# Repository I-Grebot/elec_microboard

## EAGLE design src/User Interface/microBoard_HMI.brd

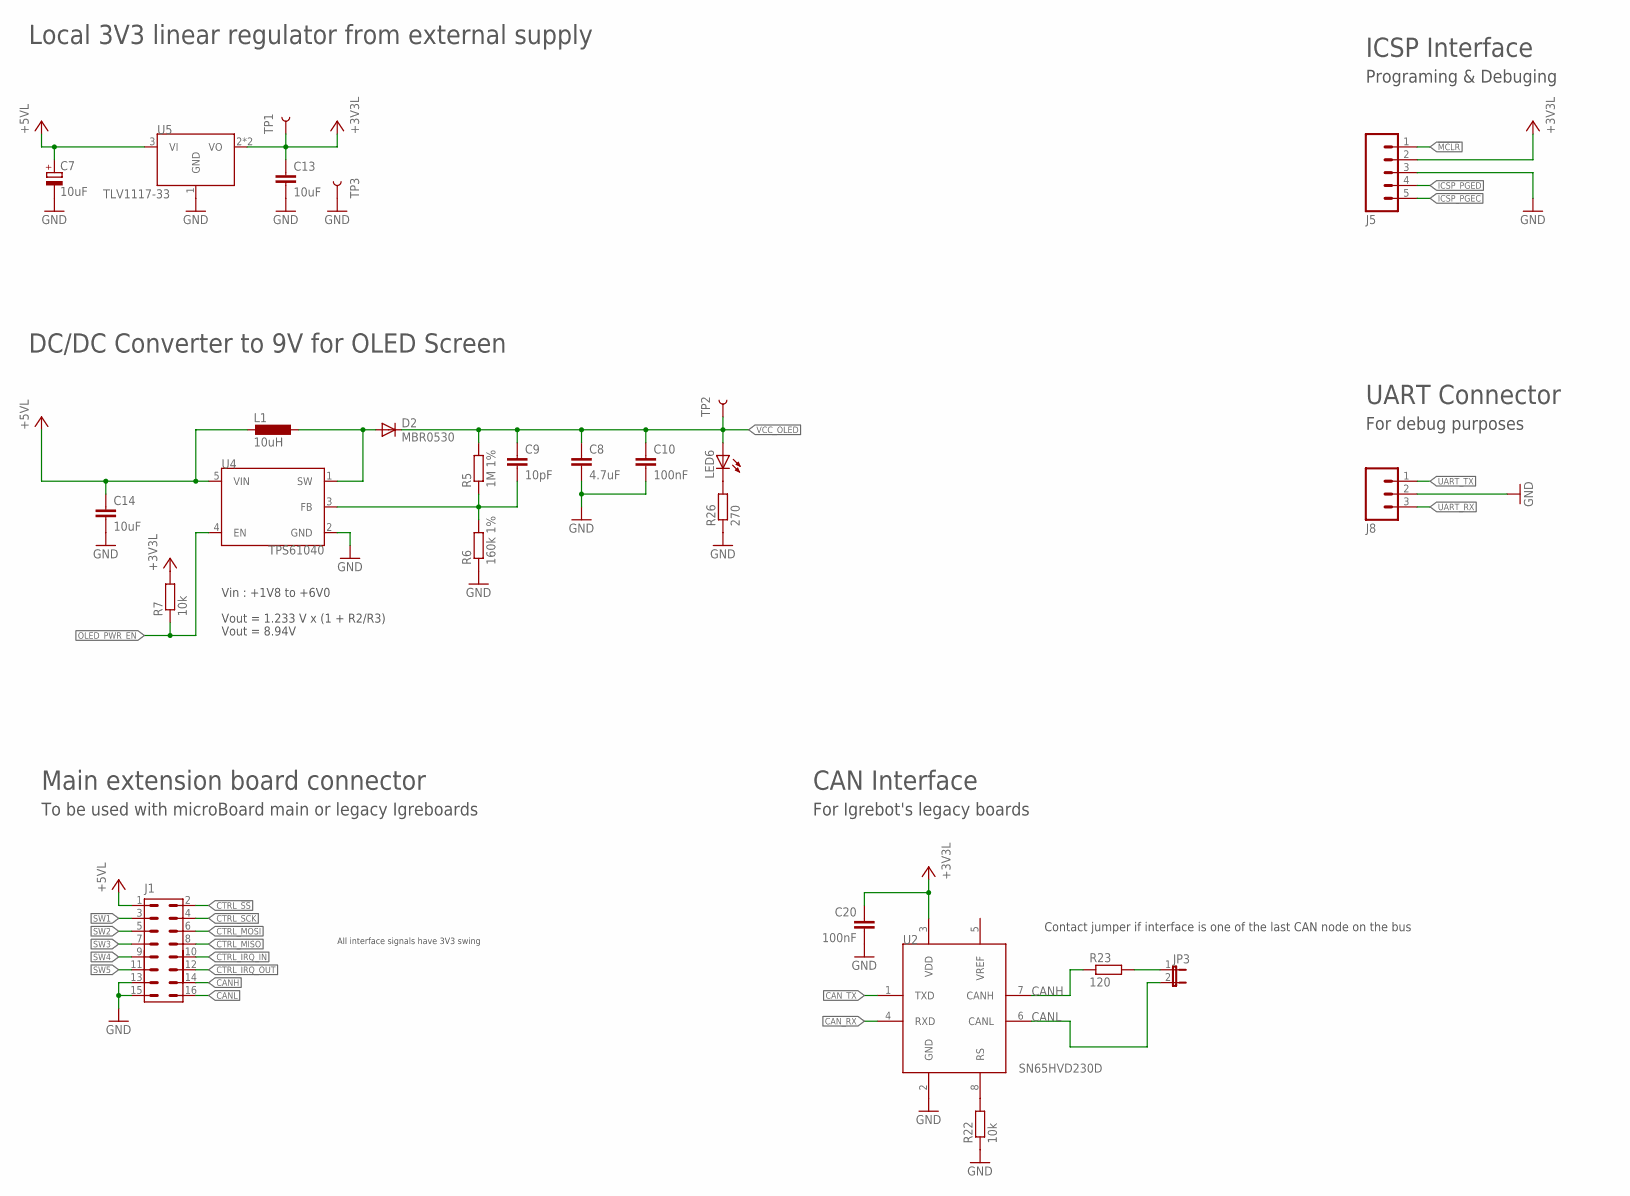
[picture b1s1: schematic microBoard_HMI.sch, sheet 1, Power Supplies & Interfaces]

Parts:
C7: 10uF; PANASONIC_C
C8: 4.7uF; C1206
C9: 10pF; C0603
C10, C20: 100nF; C0603
C13, C14: 10uF; C1206
D2: MBR0530; SOD-123_MINI-SMA
J1: HE10_H_16; CON_2X_2.54_H_16
J5: M05LOCK; 1X05_LOCK
J8: M03LOCK; 1X03_LOCK
JP3: JUMPER-2PTH_LOCK; 1X02_LOCK
L1: 10uH; L5650M
LED6: LEDCHIP-LED0805; CHIP-LED0805
R5: 1M 1%; R0603
R6: 160k 1%; R0603
R7, R22: 10k; R0603
R23: 120; R0603
R26: 270; R0603
TP1, TP2, TP3: TEST-POINT3X5; PAD.03X.05
U2: SN65HVD230D; SO-08
U4: TPS61040; SOT-23
U5: TLV1117-33; SOT_223

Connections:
!MCLR!: J5.1; also elsewhere on the board
+3V3L: C13.1, C20.1, J5.2, R7.2, TP1.P$1, U2.3 (VDD), U5.2 (VO), U5.4 (VO); also elsewhere on the board
+5VL: C7.+, C14.1, J1.1, L1.2, U4.5 (VIN), U5.3 (VI); also elsewhere on the board
CANH: J1.14, R23.1, U2.7 (CANH)
CANL: J1.16, JP3.2, U2.6 (CANL)
CAN_RX: U2.4 (RXD); also elsewhere on the board
CAN_TX: U2.1 (TXD); also elsewhere on the board
CTRL_!SS!: J1.2; also elsewhere on the board
CTRL_IRQ_IN: J1.10; also elsewhere on the board
CTRL_IRQ_OUT: J1.12; also elsewhere on the board
CTRL_MISO: J1.8; also elsewhere on the board
CTRL_MOSI: J1.6; also elsewhere on the board
CTRL_SCK: J1.4; also elsewhere on the board
GND: C7.-, C8.2, C10.2, C13.2, C14.2, C20.2, J1.13, J1.15, J5.3, J8.2, R6.1, R22.1, R26.1, TP3.P$1, U2.2 (GND), U4.2 (GND), U5.1 (GND); also elsewhere on the board
ICSP_PGEC: J5.5; also elsewhere on the board
ICSP_PGED: J5.4; also elsewhere on the board
unnamed: D2.A, L1.1, U4.1 (SW)
unnamed: C9.2, R5.1, R6.2, U4.3 (FB)
unnamed: LED6.C, R26.2
unnamed: JP3.1, R23.2
unnamed: R22.2, U2.8 (RS)
OLED_PWR_EN: R7.1, U4.4 (EN); also elsewhere on the board
SW1: J1.3; also elsewhere on the board
SW2: J1.5; also elsewhere on the board
SW3: J1.7; also elsewhere on the board
SW4: J1.9; also elsewhere on the board
SW5: J1.11; also elsewhere on the board
UART_RX: J8.3; also elsewhere on the board
UART_TX: J8.1; also elsewhere on the board
VCC_OLED: C8.1, C9.1, C10.1, D2.C, LED6.A, R5.2, TP2.P$1; also elsewhere on the board

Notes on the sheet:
Vin : +1V8 to +6V0
Vout = 1.233 V x (1 + R2/R3)
Vout = 8.94V
Local 3V3 linear regulator from external supply
DC/DC Converter to 9V for OLED Screen
To be used with microBoard main or legacy Igreboards
Main extension board connector
Programing & Debuging
ICSP Interface
All interface signals have 3V3 swing
For debug purposes
UART Connector
For Igrebot's legacy boards
CAN Interface
Contact jumper if interface is one of the last CAN node on the bus

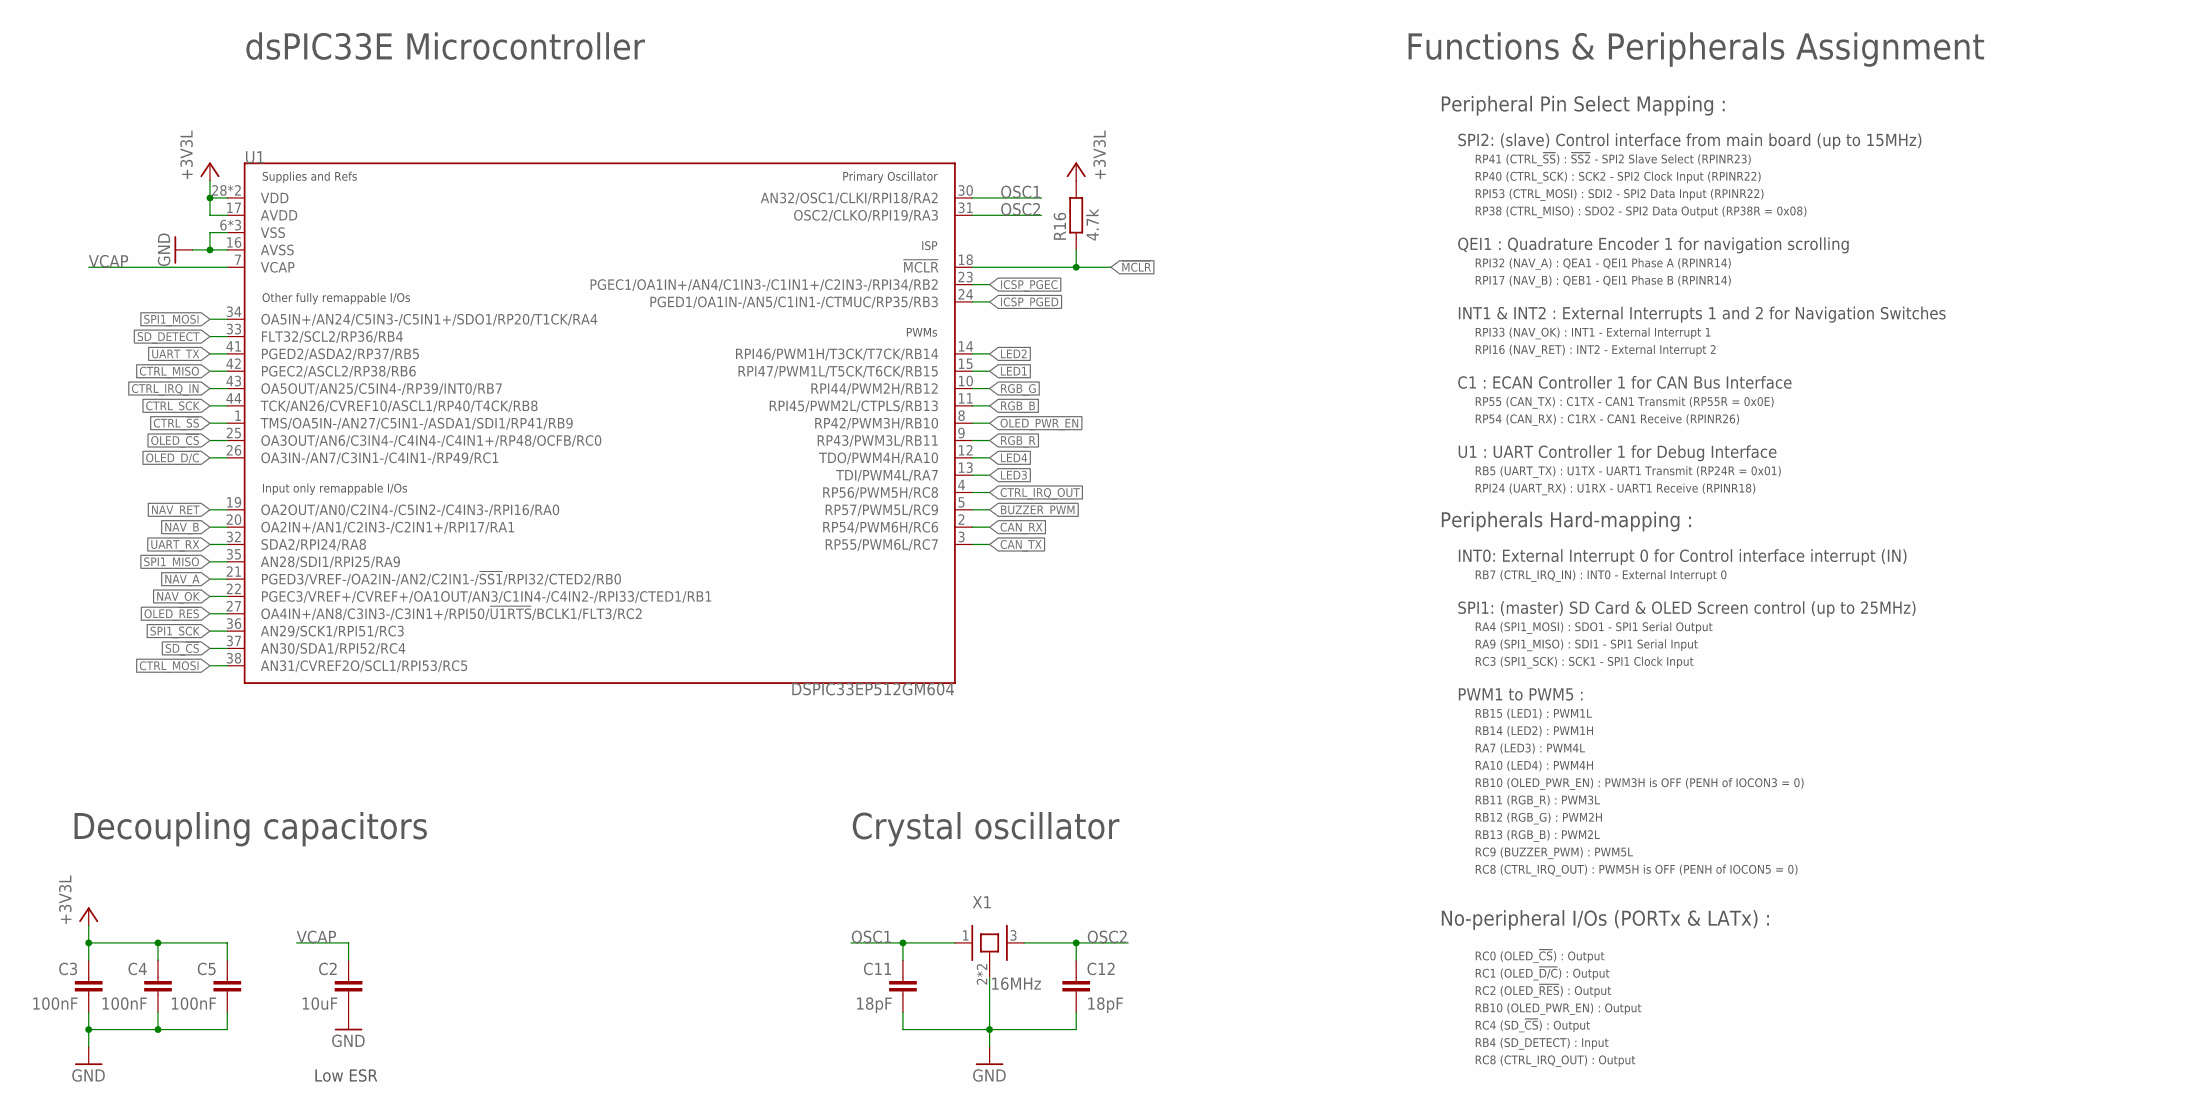
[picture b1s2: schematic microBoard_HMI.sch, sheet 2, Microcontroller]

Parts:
C2: 10uF; C1206
C3, C4, C5: 100nF; C0603
C11, C12: 18pF; C0603
R16: 4.7k; R0603
U1: DSPIC33EP512GM604; TQFP_44
X1: 16MHz; CRYSTAL-OSC-SMD-5X3

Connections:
!MCLR!: R16.1, U1.18 (!MCLR!); also elsewhere on the board
+3V3L: C3.1, C4.1, C5.1, R16.2, U1.17 (AVDD), U1.28 (VDD), U1.40 (VDD); also elsewhere on the board
BUZZER_PWM: U1.5 (RP57/PWM5L/RC9); also elsewhere on the board
CAN_RX: U1.2 (RP54/PWM6H/RC6); also elsewhere on the board
CAN_TX: U1.3 (RP55/PWM6L/RC7); also elsewhere on the board
CTRL_!SS!: U1.1 (TMS/OA5IN-/AN27/C5IN1-/ASDA1/SDI1/RP41/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); also elsewhere on the board
CTRL_IRQ_IN: U1.43 (OA5OUT/AN25/C5IN4-/RP39/INT0/RB7); also elsewhere on the board
CTRL_IRQ_OUT: U1.4 (RP56/PWM5H/RC8); also elsewhere on the board
CTRL_MISO: U1.42 (PGEC2/ASCL2/RP38/RB6); also elsewhere on the board
CTRL_MOSI: U1.38 (AN31/CVREF2O/SCL1/RPI53/RC5); also elsewhere on the board
CTRL_SCK: U1.44 (TCK/AN26/CVREF10/ASCL1/RP40/T4CK/RB8); also elsewhere on the board
GND: C2.2, C3.2, C4.2, C5.2, C11.2, C12.2, U1.6 (VSS), U1.16 (AVSS), U1.29 (VSS), U1.39 (VSS), X1.2, X1.4; also elsewhere on the board
ICSP_PGEC: U1.23 (PGEC1/OA1IN+/AN4/C1IN3-/C1IN1+/C2IN3-/R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); also elsewhere on the board
ICSP_PGED: U1.24 (PGED1/OA1IN-/AN5/C1IN1-/CTMUC/RP35/RB3); also elsewhere on the board
LED1: U1.15 (RPI47/PWM1L/T5CK/T6CK/RB15); also elsewhere on the board
LED2: U1.14 (RPI46/PWM1H/T3CK/T7CK/RB14); also elsewhere on the board
LED3: U1.13 (TDI/PWM4L/RA7); also elsewhere on the board
LED4: U1.12 (TDO/PWM4H/RA10); also elsewhere on the board
NAV_A: U1.21 (PGED3/VREF-/OA2IN-/AN2/C2IN1-/!SS1!/RPI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); also elsewhere on the board
NAV_B: U1.20 (OA2IN+/AN1/C2IN3-/C2IN1+/RPI17/RA1); also elsewhere on the board
NAV_OK: U1.22 (PGEC3/VREF+/CVREF+/OA1OUT/AN3/C1IN4-/C4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); also elsewhere on the board
NAV_RET: U1.19 (OA2OUT/AN0/C2IN4-/C5IN2-/C4IN3-/RPI16/R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); also elsewhere on the board
OLED_!CS!: U1.25 (OA3OUT/AN6/C3IN4-/C4IN4-/C4IN1+/RP48/OC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); also elsewhere on the board
OLED_!D/C!: U1.26 (OA3IN-/AN7/C3IN1-/C4IN1-/RP49/RC1); also elsewhere on the board
OLED_!RES!: U1.27 (OA4IN+/AN8/C3IN3-/C3IN1+/RPI50/!U1RTS!/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); also elsewhere on the board
OLED_PWR_EN: U1.8 (RP42/PWM3H/RB10); also elsewhere on the board
OSC1: C11.1, U1.30 (AN32/OSC1/CLKI/RPI18/RA2), X1.1
OSC2: C12.1, U1.31 (OSC2/CLKO/RPI19/RA3), X1.3
RGB_B: U1.11 (RPI45/PWM2L/CTPLS/RB13); also elsewhere on the board
RGB_G: U1.10 (RPI44/PWM2H/RB12); also elsewhere on the board
RGB_R: U1.9 (RP43/PWM3L/RB11); also elsewhere on the board
SD_!CS!: U1.37 (AN30/SDA1/RPI52/RC4); also elsewhere on the board
SD_DETECT: U1.33 (FLT32/SCL2/RP36/RB4); also elsewhere on the board
SPI1_MISO: U1.35 (AN28/SDI1/RPI25/RA9); also elsewhere on the board
SPI1_MOSI: U1.34 (OA5IN+/AN24/C5IN3-/C5IN1+/SDO1/RP20/T1C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); also elsewhere on the board
SPI1_SCK: U1.36 (AN29/SCK1/RPI51/RC3); also elsewhere on the board
UART_RX: U1.32 (SDA2/RPI24/RA8); also elsewhere on the board
UART_TX: U1.41 (PGED2/ASDA2/RP37/RB5); also elsewhere on the board
VCAP: C2.1, U1.7 (VCAP)

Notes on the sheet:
SPI2: (slave) Control interface from main board (up to 15MHz)
dsPIC33E Microcontroller
Functions & Peripherals Assignment
Decoupling capacitors
Low ESR
Crystal oscillator
Peripheral Pin Select Mapping :
RB4 (SD_DETECT) : Input
RB5 (UART_TX) : U1TX - UART1 Transmit (RP24R = 0x01)
RPI53 (CTRL_MOSI) : SDI2 - SPI2 Data Input (RPINR22)
RP38 (CTRL_MISO) : SDO2 - SPI2 Data Output (RP38R = 0x08)
RP40 (CTRL_SCK) : SCK2 - SPI2 Clock Input (RPINR22)
RP41 (CTRL_!SS!) : !SS2! - SPI2 Slave Select (RPINR23)
RC0 (OLED_!CS!) : Output
No-peripheral I/Os (PORTx & LATx) :
RC1 (OLED_!D/C!) : Output
RPI16 (NAV_RET) : INT2 - External Interrupt 2
RPI17 (NAV_B) : QEB1 - QEI1 Phase B (RPINR14)
RPI24 (UART_RX) : U1RX - UART1 Receive (RPINR18)
Peripherals Hard-mapping :
RPI32 (NAV_A) : QEA1 - QEI1 Phase A (RPINR14)
RPI33 (NAV_OK) : INT1 - External Interrupt 1
RC2 (OLED_!RES!) : Output
RC4 (SD_!CS!) : Output
RB7 (CTRL_IRQ_IN) : INT0 - External Interrupt 0
RP55 (CAN_TX) : C1TX - CAN1 Transmit (RP55R = 0x0E)
RP54 (CAN_RX) : C1RX - CAN1 Receive (RPINR26)
RB10 (OLED_PWR_EN) : Output
RC8 (CTRL_IRQ_OUT) : Output
RA4 (SPI1_MOSI) : SDO1 - SPI1 Serial Output
RA9 (SPI1_MISO) : SDI1 - SPI1 Serial Input
RC3 (SPI1_SCK) : SCK1 - SPI1 Clock Input
PWM1 to PWM5 :
SPI1: (master) SD Card & OLED Screen control (up to 25MHz)
INT1 & INT2 : External Interrupts 1 and 2 for Navigation Switches
QEI1 : Quadrature Encoder 1 for navigation scrolling
C1 : ECAN Controller 1 for CAN Bus Interface
U1 : UART Controller 1 for Debug Interface
RB15 (LED1) : PWM1L
RB14 (LED2) : PWM1H

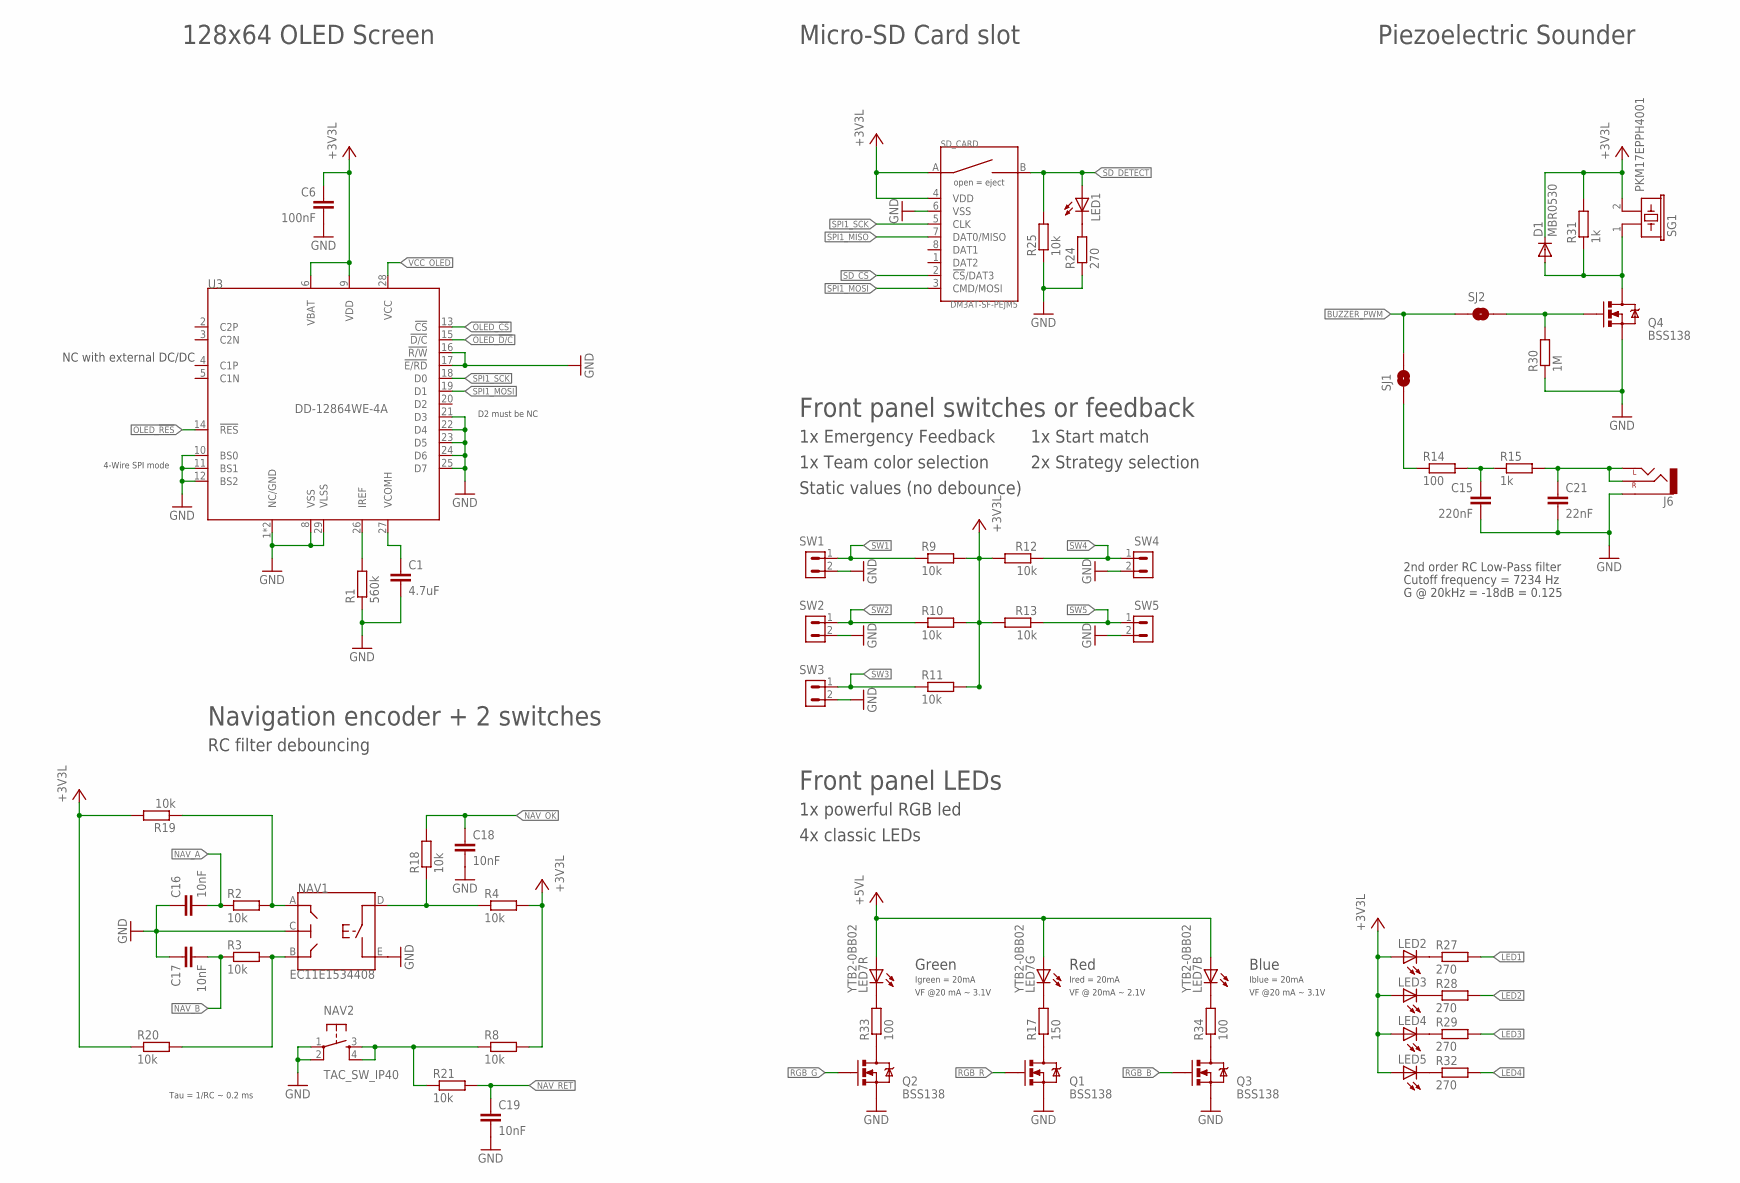
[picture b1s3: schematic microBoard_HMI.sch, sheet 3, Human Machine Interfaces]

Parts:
C1: 4.7uF; C1206
C6: 100nF; C0603
C15: 220nF; C0603
C16, C17, C18, C19: 10nF; C0603
C21: 22nF; C0603
D1: MBR0530; SOD-123_MINI-SMA
J6: AUDIO-JACK1:1; STEREOJACK2.5MM
LED1, LED2, LED3, LED4, LED5: LEDCHIP-LED0805; CHIP-LED0805
LED7: YTB2-0BB02; GM5WA94310A
NAV1: EC11E1534408
NAV2: TAC_SW_IP40
Q1, Q2, Q3, Q4: BSS138; SOT23
R1: 560k; R0603
R2, R3, R4, R8, R9, R10, R11, R12, R13, R18, R19, R20, R21, R25: 10k; R0603
R14, R33, R34: 100; R0603
R15, R31: 1k; R0603
R17: 150; R0603
R24, R27, R28, R29, R32: 270; R0603
R30: 1M; R0603
SD_CARD: DM3AT-SF-PEJM5; DM3AT
SG1: PKM17EPPH4001; F/EE17P
SJ1, SJ2: SOLDERJUMPERNC2; SJ_2S-NOTRACE
SW1, SW2, SW3, SW4, SW5: HE14_H_2
U3: DD-12864WE-4A

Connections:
+3V3L: C6.1, D1.C, LED2.A, LED3.A, LED4.A, LED5.A, R4.2, R8.2, R9.2, R10.2, R11.2, R12.2, R13.2, R19.2, R20.1, R31.2, SD_CARD.4 (VDD), SD_CARD.A, SG1.2, U3.6 (VBAT), U3.9 (VDD); also elsewhere on the board
+5VL: LED7.1 (A), LED7.2 (A), LED7.3 (A); also elsewhere on the board
BUZZER_PWM: SJ1.2, SJ2.1; also elsewhere on the board
GND: C1.2, C6.2, C15.2, C16.1, C17.1, C18.2, C19.2, C21.2, J6.5 (SLEEVE), NAV1.C, NAV1.E, NAV2.1, NAV2.2, Q1.2 (S), Q2.2 (S), Q3.2 (S), Q4.2 (S), R1.1, R24.1, R25.1, R30.1, SD_CARD.6 (VSS), SW1.2, SW2.2, SW3.2, SW4.2, SW5.2, U3.1 (NC/GND), U3.8 (VSS), U3.10 (BS0), U3.11 (BS1), U3.12 (BS2), U3.16 (!R/W!), U3.17 (!E/RD!), U3.21 (D3), U3.22 (D4), U3.23 (D5), U3.24 (D6), U3.25 (D7), U3.29 (VLSS), U3.30 (NC/GND); also elsewhere on the board
LED1: R27.2; also elsewhere on the board
LED2: R28.2; also elsewhere on the board
LED3: R29.2; also elsewhere on the board
LED4: R32.2; also elsewhere on the board
unnamed: R1.2, U3.26 (IREF)
unnamed: C1.1, U3.27 (VCOMH)
unnamed: LED7.5 (C), R33.2
unnamed: LED7.4 (C), R17.2
unnamed: LED7.6 (C), R34.2
unnamed: Q2.3 (D), R33.1
unnamed: Q1.3 (D), R17.1
unnamed: Q3.3 (D), R34.1
unnamed: C21.1, J6.1 (LEFT), J6.4 (RIGHT), R15.2
unnamed: D1.A, Q4.3 (D), R31.1, SG1.1
unnamed: C15.1, R14.2, R15.1
unnamed: R14.1, SJ1.1
unnamed: LED1.C, R24.2
unnamed: NAV1.A, R2.2, R19.1
unnamed: NAV1.B, R3.2, R20.2
unnamed: NAV1.D, R4.1, R18.1
unnamed: NAV2.3, NAV2.4, R8.1, R21.1
unnamed: Q4.1 (G), R30.2, SJ2.2
unnamed: LED2.C, R27.1
unnamed: LED3.C, R28.1
unnamed: LED4.C, R29.1
unnamed: LED5.C, R32.1
NAV_A: C16.2, R2.1; also elsewhere on the board
NAV_B: C17.2, R3.1; also elsewhere on the board
NAV_OK: C18.1, R18.2; also elsewhere on the board
NAV_RET: C19.1, R21.2; also elsewhere on the board
OLED_!CS!: U3.13 (!CS!); also elsewhere on the board
OLED_!D/C!: U3.15 (!D/C!); also elsewhere on the board
OLED_!RES!: U3.14 (!RES!); also elsewhere on the board
RGB_B: Q3.1 (G); also elsewhere on the board
RGB_G: Q2.1 (G); also elsewhere on the board
RGB_R: Q1.1 (G); also elsewhere on the board
SD_!CS!: SD_CARD.2 (!CS!/DAT3); also elsewhere on the board
SD_DETECT: LED1.A, R25.2, SD_CARD.B; also elsewhere on the board
SPI1_MISO: SD_CARD.7 (DAT0/MISO); also elsewhere on the board
SPI1_MOSI: SD_CARD.3 (CMD/MOSI), U3.19 (D1); also elsewhere on the board
SPI1_SCK: SD_CARD.5 (CLK), U3.18 (D0); also elsewhere on the board
SW1: R9.1, SW1.1; also elsewhere on the board
SW2: R10.1, SW2.1; also elsewhere on the board
SW3: R11.1, SW3.1; also elsewhere on the board
SW4: R12.1, SW4.1; also elsewhere on the board
SW5: R13.1, SW5.1; also elsewhere on the board
VCC_OLED: U3.28 (VCC); also elsewhere on the board

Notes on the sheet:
4-Wire SPI mode
D2 must be NC
NC with external DC/DC
Green
Red
Blue
VF @ 20mA ~ 2.1V
VF @20 mA ~ 3.1V
Igreen = 20mA
Iblue = 20mA
Ired = 20mA
128x64 OLED Screen
1x Emergency Feedback
Micro-SD Card slot
Navigation encoder + 2 switches
Front panel LEDs
Front panel switches or feedback
1x Team color selection
1x Start match
2x Strategy selection
1x powerful RGB led
4x classic LEDs
Piezoelectric Sounder
RC filter debouncing
Tau = 1/RC ~ 0.2 ms
Static values (no debounce)
Cutoff frequency = 7234 Hz
2nd order RC Low-Pass filter
G @ 20kHz = -18dB = 0.125

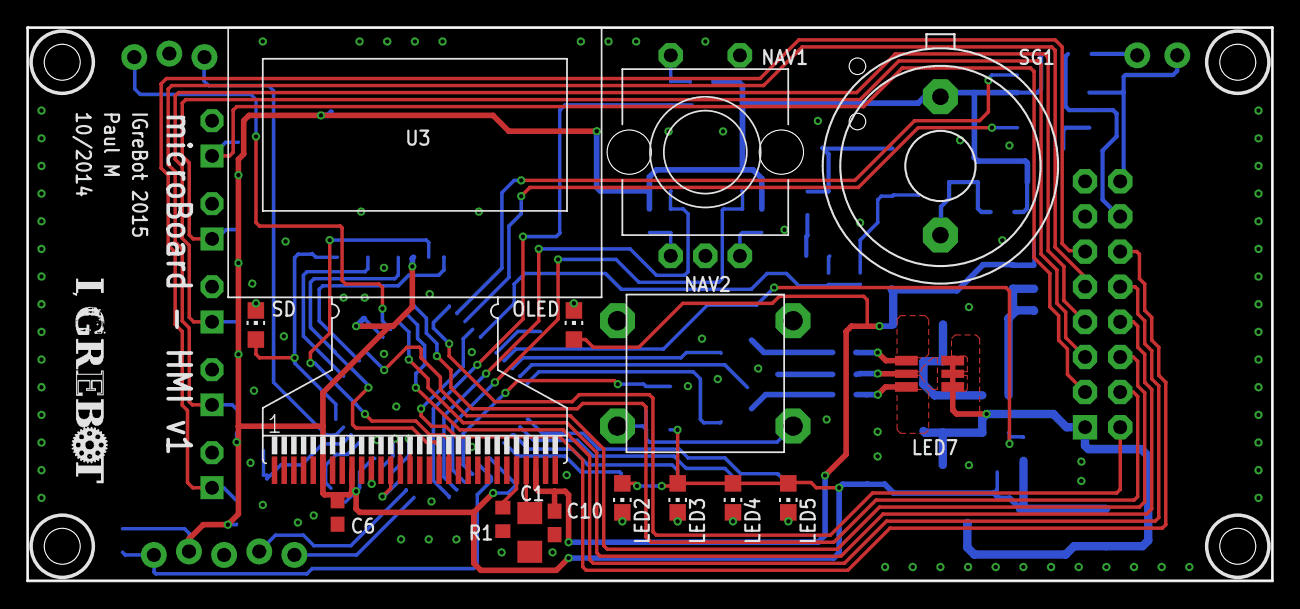
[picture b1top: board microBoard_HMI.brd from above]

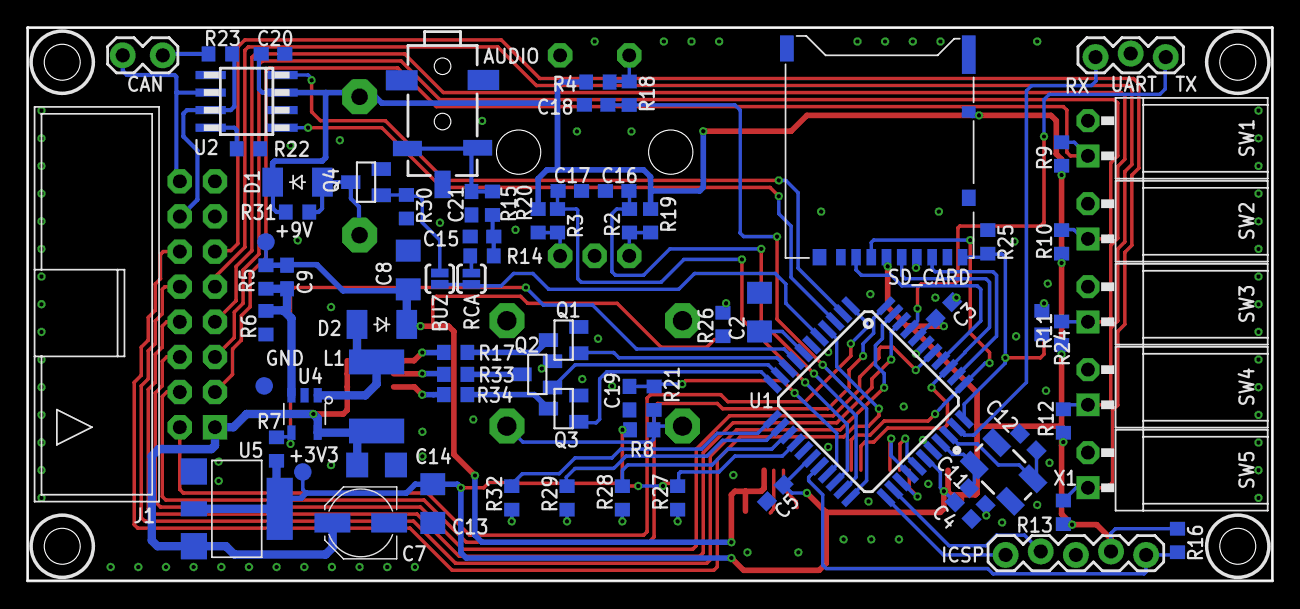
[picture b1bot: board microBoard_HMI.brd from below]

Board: 2 copper layers, 90.0 x 40.0 mm, 94 parts (79 on the bottom side), 75 nets.

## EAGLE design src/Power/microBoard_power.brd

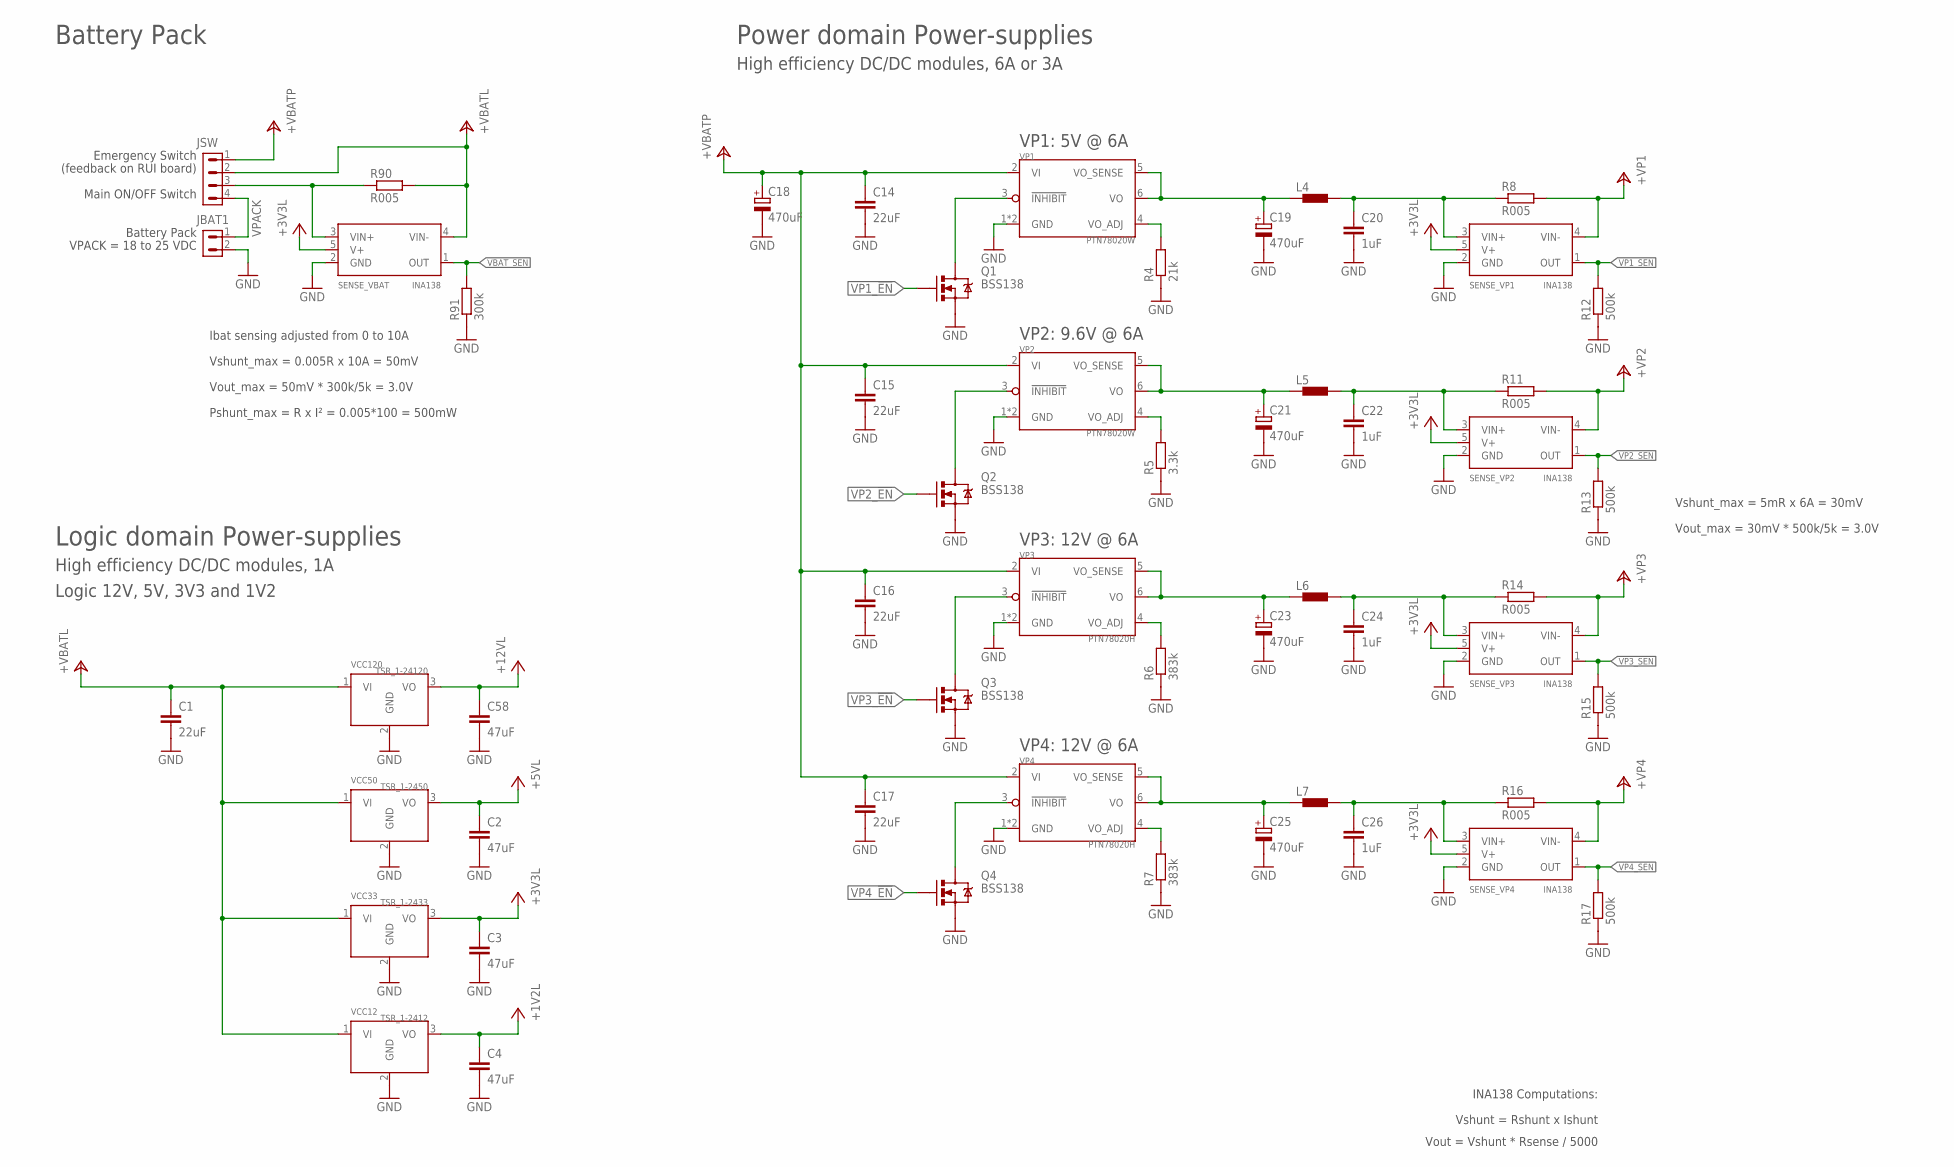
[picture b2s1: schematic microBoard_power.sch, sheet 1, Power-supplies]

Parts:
C1, C14, C15, C16, C17: 22uF; C3225
C2, C3, C4, C58: 47uF; C1210
C18: 470uF; PANASONIC_B
C19, C21, C23, C25: 470uF; PANASONIC_D
C20, C22, C24, C26: 1uF; C3225
JBAT1: MC15-GF-3.81-LR_2; CON_3.81_LR_2
JSW: MC15-GF-3.81-LR_4; CON_3.81_LR_4
L4, L5, L6, L7: DR1030
Q1, Q2, Q3, Q4: BSS138; SOT23
R4: 21k; R0603
R5: 3.3k; R0603
R6, R7: 383k; R0603
R8, R11, R14, R16, R90: R005; R2512
R12, R13, R15, R17: 500k; R0603
R91: 300k; R0603
SENSE_VBAT: INA138; DBV_05
SENSE_VP1, SENSE_VP2, SENSE_VP3, SENSE_VP4: INA138; DBV_05
VCC12: TSR_1-2412; TSR1
VCC33: TSR_1-2433; TSR1
VCC50: TSR_1-2450; TSR1
VCC120: TSR_1-24120; TSR1
VP1, VP2: PTN78020W; PTN78020
VP3, VP4: PTN78020H; PTN78020

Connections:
!INHIBIT!_VP1: Q1.3 (D), VP1.3 (!INHIBIT!)
!INHIBIT!_VP5: Q2.3 (D), VP2.3 (!INHIBIT!)
!INHIBIT!_VP6: Q3.3 (D), VP3.3 (!INHIBIT!)
!INHIBIT!_VP7: Q4.3 (D), VP4.3 (!INHIBIT!)
+1V2L: C4.1, VCC12.3 (VO); also elsewhere on the board
+3V3L: C3.1, SENSE_VBAT.5 (V+), SENSE_VP1.5 (V+), SENSE_VP2.5 (V+), SENSE_VP3.5 (V+), SENSE_VP4.5 (V+), VCC33.3 (VO); also elsewhere on the board
+5VL: C2.1, VCC50.3 (VO); also elsewhere on the board
+12VL: C58.1, VCC120.3 (VO); also elsewhere on the board
+VBATL: C1.1, JSW.2, R90.2, SENSE_VBAT.4 (VIN-), VCC12.1 (VI), VCC33.1 (VI), VCC50.1 (VI), VCC120.1 (VI)
+VBATP: C14.1, C15.1, C16.1, C17.1, C18.+, JSW.1, VP1.2 (VI), VP2.2 (VI), VP3.2 (VI), VP4.2 (VI); also elsewhere on the board
+VP1: R8.2, SENSE_VP1.4 (VIN-); also elsewhere on the board
+VP2: R11.2, SENSE_VP2.4 (VIN-); also elsewhere on the board
+VP3: R14.2, SENSE_VP3.4 (VIN-); also elsewhere on the board
+VP4: R16.2, SENSE_VP4.4 (VIN-); also elsewhere on the board
GND: C1.2, C2.2, C3.2, C4.2, C14.2, C15.2, C16.2, C17.2, C18.-, C19.-, C20.2, C21.-, C22.2, C23.-, C24.2, C25.-, C26.2, C58.2, JBAT1.2, Q1.2 (S), Q2.2 (S), Q3.2 (S), Q4.2 (S), R4.1, R5.1, R6.1, R7.1, R12.1, R13.1, R15.1, R17.1, R91.1, SENSE_VBAT.2 (GND), SENSE_VP1.2 (GND), SENSE_VP2.2 (GND), SENSE_VP3.2 (GND), SENSE_VP4.2 (GND), VCC12.2 (GND), VCC33.2 (GND), VCC50.2 (GND), VCC120.2 (GND), VP1.1 (GND), VP1.7 (GND), VP2.1 (GND), VP2.7 (GND), VP3.1 (GND), VP3.7 (GND), VP4.1 (GND), VP4.7 (GND); also elsewhere on the board
unnamed: C19.+, L4.1, VP1.5 (VO_SENSE), VP1.6 (VO)
unnamed: R7.2, VP4.4 (VO_ADJ)
unnamed: C20.1, L4.2, R8.1, SENSE_VP1.3 (VIN+)
unnamed: R6.2, VP3.4 (VO_ADJ)
unnamed: R5.2, VP2.4 (VO_ADJ)
unnamed: C21.+, L5.1, VP2.5 (VO_SENSE), VP2.6 (VO)
unnamed: R4.2, VP1.4 (VO_ADJ)
unnamed: C22.1, L5.2, R11.1, SENSE_VP2.3 (VIN+)
unnamed: C23.+, L6.1, VP3.5 (VO_SENSE), VP3.6 (VO)
unnamed: C24.1, L6.2, R14.1, SENSE_VP3.3 (VIN+)
unnamed: C25.+, L7.1, VP4.5 (VO_SENSE), VP4.6 (VO)
unnamed: C26.1, L7.2, R16.1, SENSE_VP4.3 (VIN+)
unnamed: JSW.3, R90.1, SENSE_VBAT.3 (VIN+)
VBAT_SEN: R91.2, SENSE_VBAT.1 (OUT); also elsewhere on the board
VP1_!EN!: Q1.1 (G); also elsewhere on the board
VP1_SEN: R12.2, SENSE_VP1.1 (OUT); also elsewhere on the board
VP2_!EN!: Q2.1 (G); also elsewhere on the board
VP2_SEN: R13.2, SENSE_VP2.1 (OUT); also elsewhere on the board
VP3_!EN!: Q3.1 (G); also elsewhere on the board
VP3_SEN: R15.2, SENSE_VP3.1 (OUT); also elsewhere on the board
VP4_!EN!: Q4.1 (G); also elsewhere on the board
VP4_SEN: R17.2, SENSE_VP4.1 (OUT); also elsewhere on the board
VPACK: JBAT1.1, JSW.4

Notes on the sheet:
VP1: 5V @ 6A
VP2: 9.6V @ 6A
VP3: 12V @ 6A
VP4: 12V @ 6A
Logic 12V, 5V, 3V3 and 1V2
VPACK = 18 to 25 VDC
Logic domain Power-supplies
High efficiency DC/DC modules, 1A
Power domain Power-supplies
High efficiency DC/DC modules, 6A or 3A
Battery Pack
Vshunt = Rshunt x Ishunt
Vout = Vshunt * Rsense / 5000
Vshunt_max = 5mR x 6A = 30mV
Vout_max = 30mV * 500k/5k = 3.0V
Emergency Switch
Main ON/OFF Switch
(feedback on RUI board)
Vshunt_max = 0.005R x 10A = 50mV
Vout_max = 50mV * 300k/5k = 3.0V
Ibat sensing adjusted from 0 to 10A
INA138 Computations:
Pshunt_max = R x I² = 0.005*100 = 500mW

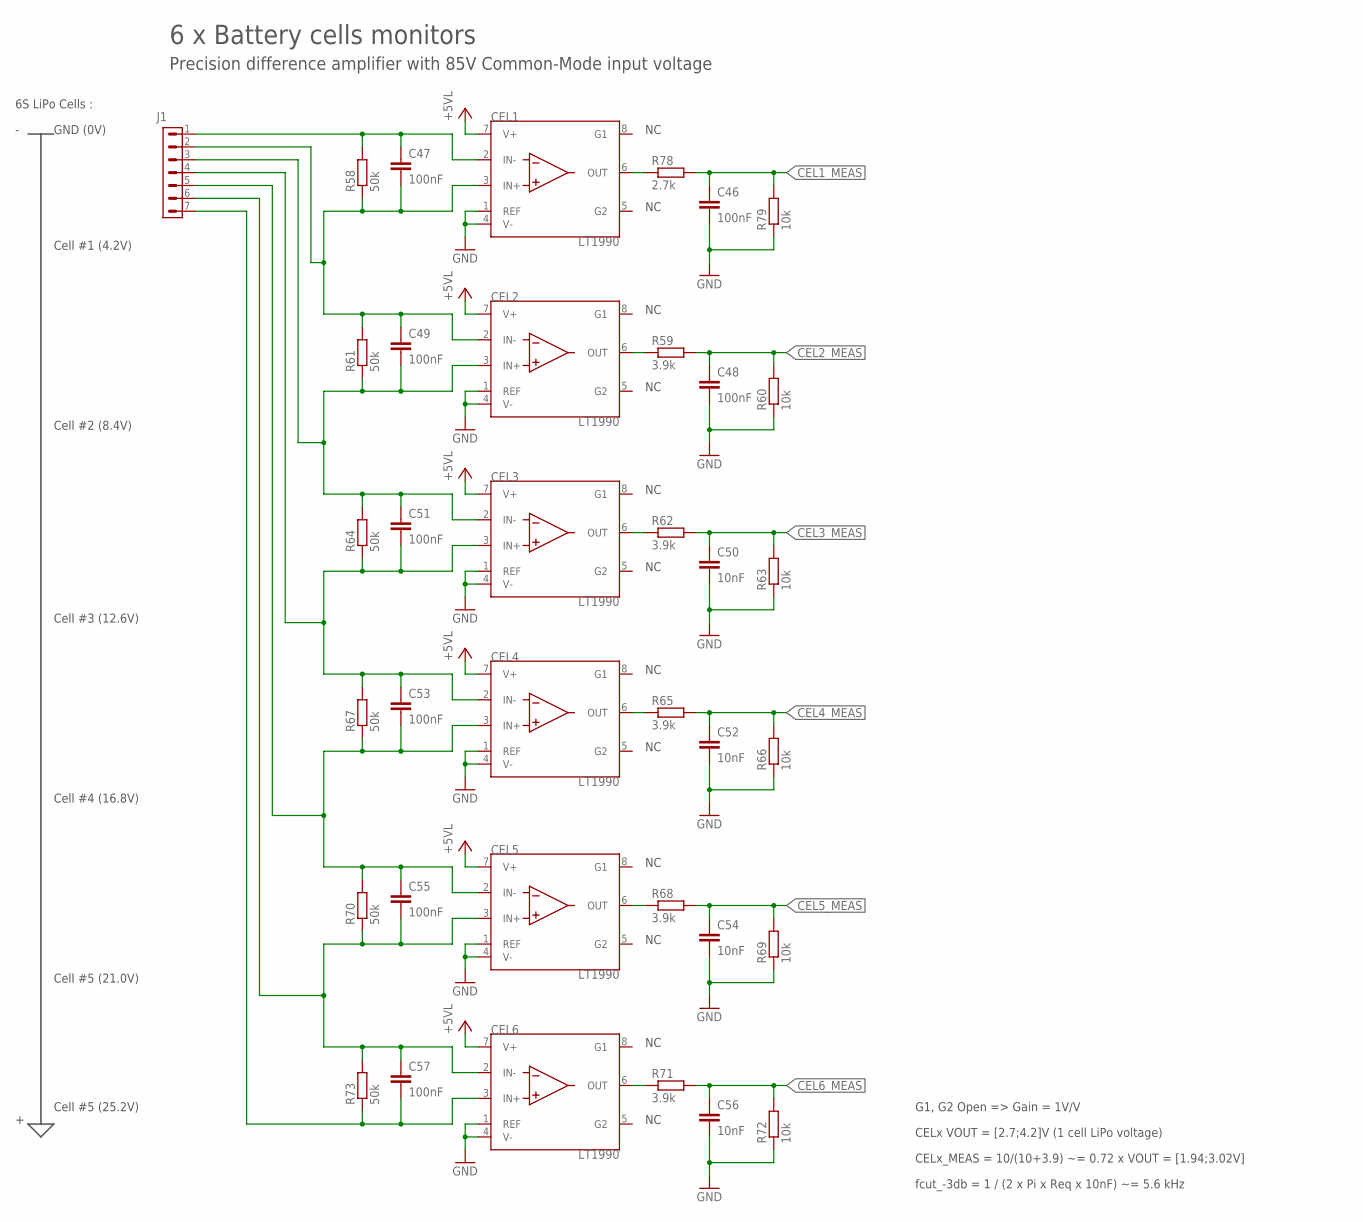
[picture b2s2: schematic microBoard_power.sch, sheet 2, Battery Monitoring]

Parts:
C46, C47, C48, C49, C51, C53, C55, C57: 100nF; C0603
C50, C52, C54, C56: 10nF; C0603
CEL1, CEL2, CEL3, CEL4, CEL5, CEL6: LT1990; S8
J1: JST-XH-S_7; JST-XH-7S
R58, R61, R64, R67, R70, R73: 50k; R0603
R59, R62, R65, R68, R71: 3.9k; R0603
R60, R63, R66, R69, R72, R79: 10k; R0603
R78: 2.7k; R0603

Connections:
+5VL: CEL1.7 (V+), CEL2.7 (V+), CEL3.7 (V+), CEL4.7 (V+), CEL5.7 (V+), CEL6.7 (V+); also elsewhere on the board
CEL1_MEAS: C46.1, R78.2, R79.2; also elsewhere on the board
CEL2_MEAS: C48.1, R59.2, R60.2; also elsewhere on the board
CEL3_MEAS: C50.1, R62.2, R63.2; also elsewhere on the board
CEL4_MEAS: C52.1, R65.2, R66.2; also elsewhere on the board
CEL5_MEAS: C54.1, R68.2, R69.2; also elsewhere on the board
CEL6_MEAS: C56.1, R71.2, R72.2; also elsewhere on the board
GND: C46.2, C48.2, C50.2, C52.2, C54.2, C56.2, CEL1.1 (REF), CEL1.4 (V-), CEL2.1 (REF), CEL2.4 (V-), CEL3.1 (REF), CEL3.4 (V-), CEL4.1 (REF), CEL4.4 (V-), CEL5.1 (REF), CEL5.4 (V-), CEL6.1 (REF), CEL6.4 (V-), R60.1, R63.1, R66.1, R69.1, R72.1, R79.1; also elsewhere on the board
unnamed: CEL1.6 (OUT), R78.1
unnamed: C47.1, CEL1.2 (IN-), J1.1, R58.2
unnamed: C47.2, C49.1, CEL1.3 (IN+), CEL2.2 (IN-), J1.2, R58.1, R61.2
unnamed: CEL2.6 (OUT), R59.1
unnamed: C49.2, C51.1, CEL2.3 (IN+), CEL3.2 (IN-), J1.3, R61.1, R64.2
unnamed: CEL3.6 (OUT), R62.1
unnamed: C51.2, C53.1, CEL3.3 (IN+), CEL4.2 (IN-), J1.4, R64.1, R67.2
unnamed: CEL4.6 (OUT), R65.1
unnamed: C53.2, C55.1, CEL4.3 (IN+), CEL5.2 (IN-), J1.5, R67.1, R70.2
unnamed: CEL5.6 (OUT), R68.1
unnamed: C55.2, C57.1, CEL5.3 (IN+), CEL6.2 (IN-), J1.6, R70.1, R73.2
unnamed: CEL6.6 (OUT), R71.1
unnamed: C57.2, CEL6.3 (IN+), J1.7, R73.1

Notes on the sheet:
G1, G2 Open => Gain = 1V/V
CELx VOUT = [2.7;4.2]V (1 cell LiPo voltage)
CELx_MEAS = 10/(10+3.9) ~= 0.72 x VOUT = [1.94;3.02V]
6S LiPo Cells :
GND (0V)
Cell #1 (4.2V)
Cell #2 (8.4V)
Cell #3 (12.6V)
Cell #4 (16.8V)
Cell #5 (21.0V)
Cell #5 (25.2V)
6 x Battery cells monitors
Precision difference amplifier with 85V Common-Mode input voltage
fcut_-3db = 1 / (2 x Pi x Req x 10nF) ~= 5.6 kHz

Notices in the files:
parts and their libraries:
SparkFun-Connectors: Licensing: Creative Commons ShareAlike 4.0 International - https://creativecommons.org/licenses/by-sa/4.0
SparkFun-Passives: Licensing: CC v3.0 Share-Alike You are welcome to use this library for commercial purposes.
